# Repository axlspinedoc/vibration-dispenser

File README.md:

<h3 align="center">Dispensador Vibratorio</h3>

<div align="center">

</div>

---

<p align="center"> Automatización de un equipo dispensador de alimentos a granel
    <br> 
</p>

# 🧐 Acerca del proyecto 

Este repositorio contiene el código fuente del sistema operativo de una dispensador a granel utilizando un microcontrolador Amega2560

# 🏁 Preparación necesaria 

1. Instale la herramienta [VSCode](https://code.visualstudio.com)

2. Abra el programa y entre a _File_, _Preferences_, _Extensions_.

3. En el buscador, introduzca _C/C++_ e instale la extensión.

4. Nuevamente en el buscador, introduzca ahora _PlatformIO IDE_ e instale.

5. Una vez instalados correctamente, cada vez que abra VSCode aparecerá la pantalla de inicio con el anuncio "Welcome to PlatformIO"

6. Descargue una copia de este repositorio desde la opción _Code_, _Descargar Zip_. Descomprima en una ubicación conocida.

7. Desde la pestaña de _home_ de PlatformIO, seleccione _import Arduino project_

8. El programa cargara el proyecto y actualizará los documentos dependiendo la computadora donde se abra. *Espere 5 minutos*, esto permitirá que esté listo para programar

9. Para verificar que está listo busque el botón _Build_ en la barra inferior azul, marcado con el símbolo de palomilla

10. Si en el panel inferior aparece la instrucción [SUCCESS], está listo para programar. Conecte el Arduino a su computadora con el cable USB

11. Presione el botón _Upload_ en la barra inferior azul, marcado con una flecha hacia la derecha. Este botón está inmediatamente a la derecha del botón con la palomilla.

12. Pasados 15 segundos, el _Arduino_ se habrá reinicializado. ¡Ha actualizado exitosamente su microcontrolador!

# Para realizar Ajustes

Abra el archivo _utilities.h_ dentro de la carpeta _lib/inc_

Desde aquí puede editarse:

1. Producto a cargar al iniciar el equipo
2. Peso inicial default
3. Tiempo de espera cuando termina de vaciarse la Tolva
4. Selección del modo del relevador
5. Posiciones de la puerta en el estado ABIERTO y CERRADO
6. Sensibilidad de la báscula durante dispensado y vaciado
7. Calibración de báscula
8. Tiempo de señal de _Relay_
9. Tiempo de espera después de dispensar en tolva

Para editar la base de datos de productos abra el archivo _productos.h_ dentro de la carpeta _lib/inc_

Siga las indicaciones del archivo para agregar productos seleccionables desde la pantalla

# ⛏️ Built Using 

- [Visual Studio Code](https://code.visualstudio.com) - IDE
- [PlatformIO](https://platformio.org) - Embedded development IDE
- [Arduino Mega](https://www.arduino.cc) - Prototyping

# ✍️ Authors 

- [@axlspinedoc](https://github.com/axlspinedoc) - Developer

# 🎉 Acknowledgements 

- Amber Macias

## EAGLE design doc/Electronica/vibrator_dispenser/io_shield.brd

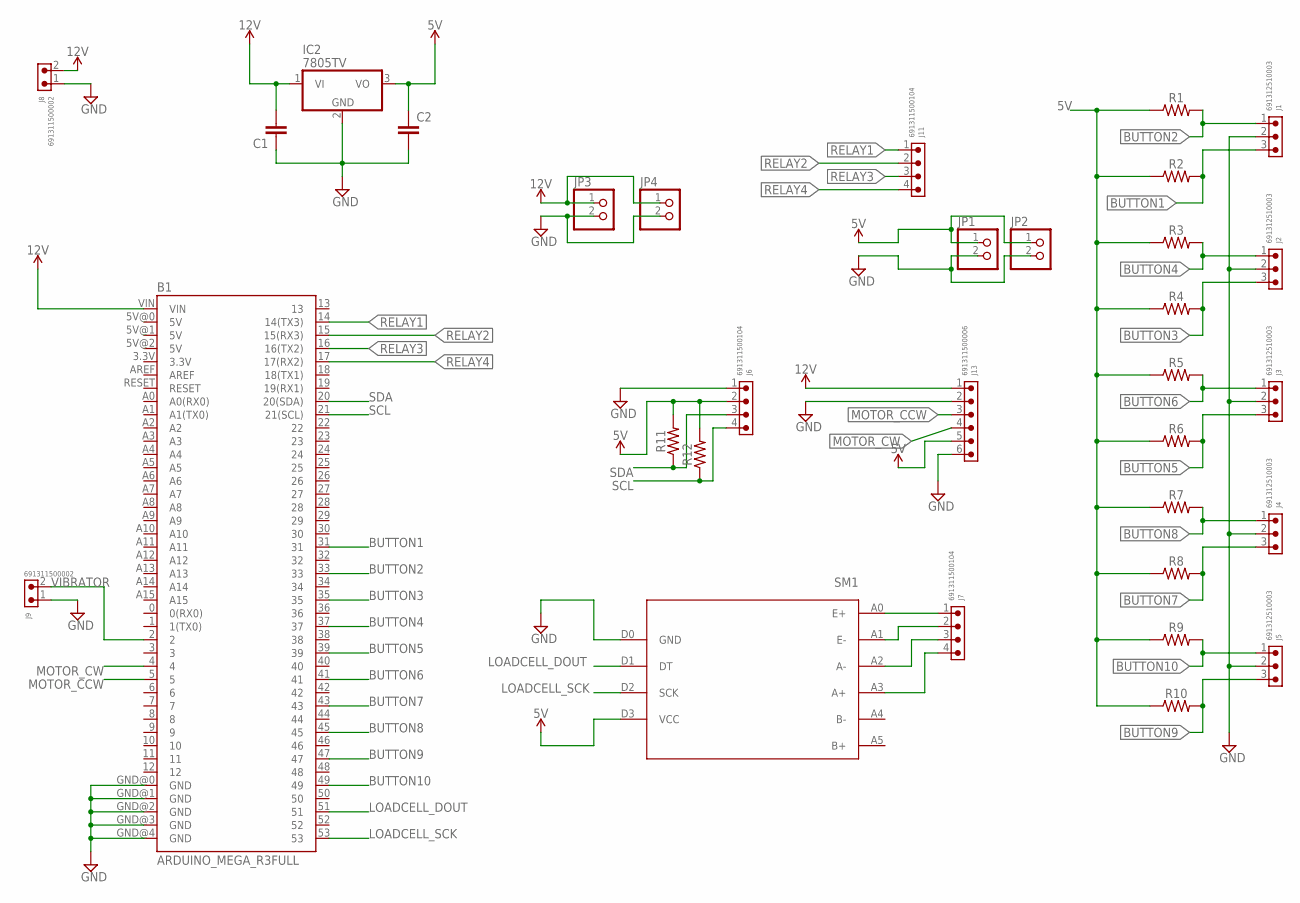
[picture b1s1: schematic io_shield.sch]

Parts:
B1: ARDUINO_MEGA_R3FULL; ARDUINO_MEGA
C1, C2: C-EU050-025X075; C050-025X075
IC2: 7805TV; TO220V
J1, J2, J3, J4, J5: 691312510003
J6, J7, J11: 691311500104
J8, J9: 691311500002
J13: 691311500006
JP1, JP2, JP3, JP4: PINHD-1X2; 1X02
R1, R2, R3, R4, R5, R6, R7, R8, R9, R10, R11, R12: AXIAL-0.3
SM1: HX711

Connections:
5V: C2.1, IC2.3 (VO), J6.2, J13.5, JP1.1, JP2.1, R1.P$1 (1), R2.P$1 (1), R3.P$1 (1), R4.P$1 (1), R5.P$1 (1), R6.P$1 (1), R7.P$1 (1), R8.P$1 (1), R9.P$1 (1), R10.P$1 (1), R11.P$2 (2), R12.P$2 (2), SM1.D3 (VCC)
12V: B1.VIN, C1.2, IC2.1 (VI), J8.2, J13.1, JP3.1, JP4.1
A+: J7.4, SM1.A3 (A+)
A-: J7.3, SM1.A2 (A-)
BUTTON1: B1.31, J1.3, R2.P$2 (2)
BUTTON2: B1.33, J1.1, R1.P$2 (2)
BUTTON3: B1.35, J2.3, R4.P$2 (2)
BUTTON4: B1.37, J2.1, R3.P$2 (2)
BUTTON5: B1.39, J3.3, R6.P$2 (2)
BUTTON6: B1.41, J3.1, R5.P$2 (2)
BUTTON7: B1.43, J4.3, R8.P$2 (2)
BUTTON8: B1.45, J4.1, R7.P$2 (2)
BUTTON9: B1.47, J5.3, R10.P$2 (2)
BUTTON10: B1.49, J5.1, R9.P$2 (2)
E+: J7.1, SM1.A0 (E+)
E-: J7.2, SM1.A1 (E-)
GND: B1.GND@0 (GND), B1.GND@1 (GND), B1.GND@2 (GND), B1.GND@3 (GND), B1.GND@4 (GND), C1.1, C2.2, IC2.2 (GND), J1.2, J2.2, J3.2, J4.2, J5.2, J6.1, J8.1, J9.1, J13.2, J13.6, JP1.2, JP2.2, JP3.2, JP4.2, SM1.D0 (GND)
LOADCELL_DOUT: B1.51, SM1.D1 (DT)
LOADCELL_SCK: B1.53, SM1.D2 (SCK)
MOTOR_CCW: B1.5, J13.3
MOTOR_CW: B1.4, J13.4
RELAY1: B1.14 (14(TX3)), J11.1
RELAY2: B1.15 (15(RX3)), J11.2
RELAY3: B1.16 (16(TX2)), J11.3
RELAY4: B1.17 (17(RX2)), J11.4
SCL: B1.21 (21(SCL)), J6.4, R12.P$1 (1)
SDA: B1.20 (20(SDA)), J6.3, R11.P$1 (1)
VIBRATOR: B1.2, J9.2

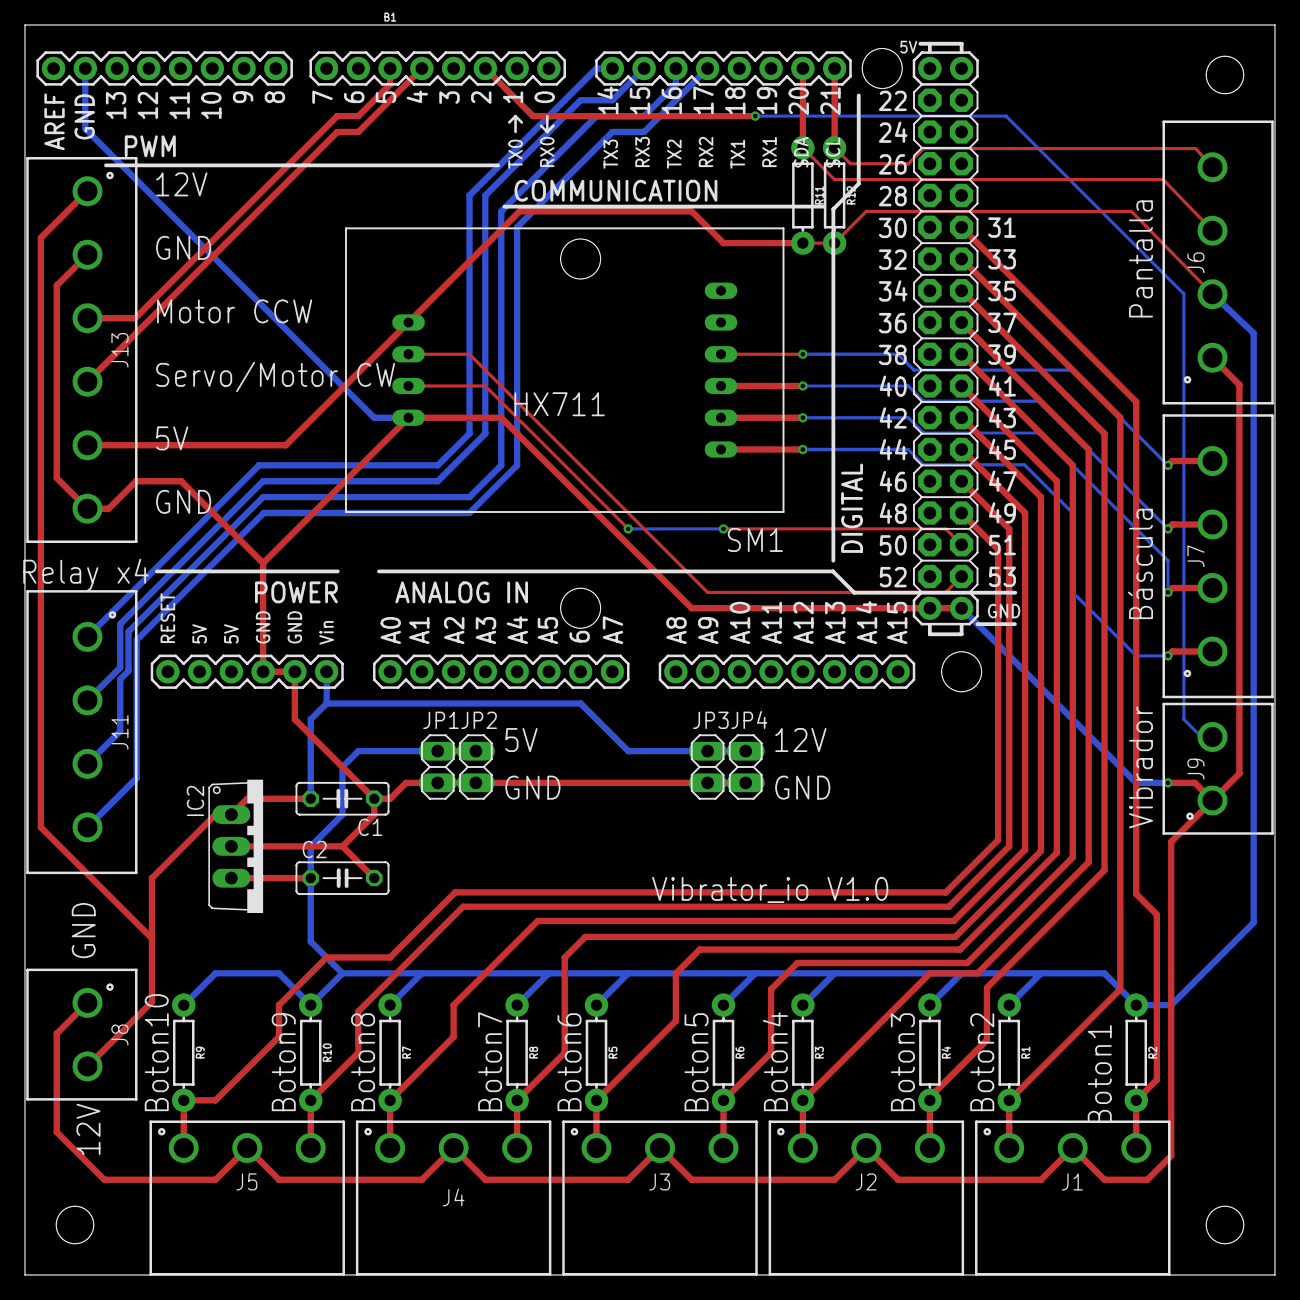
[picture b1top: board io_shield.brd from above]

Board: 2 copper layers, 100.0 x 100.0 mm, 32 parts (0 on the bottom side), 28 nets.

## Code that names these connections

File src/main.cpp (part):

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  analogWrite(DC_CW_PIN,0);
  #endif

  scale.begin(LOADCELL_DOUT_PIN, LOADCELL_SCK_PIN);  
  
  //if (scale.wait_ready_retry(20,100))  
  if (scale.is_ready())
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  setScreen(Screen::STANDBY);  
  
  // Vibrator
  pinMode(VIBRATOR_PIN, OUTPUT);

  // Relays
  pinMode(RELAY1_PIN,OUTPUT); // Vibrador para Tolva
  pinMode(RELAY2_PIN,OUTPUT); // Alarma
  pinMode(RELAY3_PIN,OUTPUT); // Chicharra
  pinMode(RELAY4_PIN,OUTPUT); // --Libre--
  
  // Relay behavior is inverted
  digitalWrite(RELAY1_PIN,HIGH);
  digitalWrite(RELAY2_PIN,HIGH);
  digitalWrite(RELAY3_PIN,HIGH);
  digitalWrite(RELAY4_PIN,HIGH);

}

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        
        // From here, we will delay 2s and jump right into FLUSH
        delay(delay_after_dispense);                
        digitalWrite(RELAY1_PIN,LOW);
                        
        machine_state.setState(control::State::SERVED);        

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      {        
        cancel_button.reset();
        delay(door_delay);
        digitalWrite(RELAY1_PIN,HIGH);                
                                
        timer_alarma=millis();
        
        // Relevador para ALARMA
        digitalWrite(RELAY2_PIN,LOW);        
        while((millis()-timer_alarma)<relay_delay){
          
          if (wrong_weight==true)
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          }
                                        
        }
        digitalWrite(RELAY2_PIN,HIGH);
        digitalWrite(RELAY3_PIN,HIGH);
        buzzer_on=false;
        // erase flag
        wrong_weight=false;
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        if (checkArrowButtons()==Key::SELECT)
        {
          incomingChar='.';
          digitalWrite(RELAY1_PIN,HIGH);
          digitalWrite(RELAY2_PIN,HIGH);
          digitalWrite(RELAY3_PIN,HIGH);
          digitalWrite(RELAY4_PIN,HIGH);
          resetArrowButtons();
          machine_state.setState(control::State::STANDBY);
          setScreen(Screen::STANDBY);
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  {
    if (buzzer_on==true)
    {
      digitalWrite(RELAY3_PIN, HIGH);
      buzzer_on = false;
    }else
    {
      digitalWrite(RELAY3_PIN, LOW);
      buzzer_on = true;
    }
    previous_buzzer_timestamp=millis();    
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
void setVibration(int percentage){
  //int pwm=map(percentage,0,100,0,255);
  //analogWrite(VIBRATOR_PIN,pwm);
  analogWrite(VIBRATOR_PIN,percentage);
}

void errorScreen(String msg){
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
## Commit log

2020-09-14 Created project in PIO
2020-09-16 updated git ignore, added template for clases
2020-09-16 Added some libraries, building simple state machine
2020-09-16 Successful test of State machine. TODO: Test weight change
2020-09-16 Implemented state machine class
2020-09-16 Added library for load cell
2020-09-16 Added liquid crystal library
2020-09-18 Added support for LCD using PIO library
2020-09-18 Added LCD functionality for MH LCDI2C Adapter, replaced previous library. TODO: Implement one time only LCD prints
2020-09-18 MVP with state machine and 20x4 LCD
2020-09-18 Defined keypad library and keys enum
2020-09-18 Added screencom library with functions for each type of menu
2020-09-18 Added support for keypad shield LCD
2020-09-18 Created readme.md with template
2020-09-19 Added keypad library
2020-09-19 Changed board to Arduino Mega
2020-09-19 WIP LCD Debugging, possible bad LCD
2020-09-19 Keypad shield and Arduino Mega fully functional
2020-09-20 WIP button library, broken atm
2020-09-20 Changed button behavior
2020-09-20 Button library fully functional
2020-09-20 Implemented buttons to main. TODO Debug SERVED Stage
2020-09-20 Corrected button logic inside main. Buttons finalized
2020-09-20 Changed tick() function to update() inside button to better reflect behavior
2020-09-20 Keypad functionality testing. WIP Debounce for directional keys
2020-09-20 Testing debounce routine inside Keypad
2020-09-20 WIP Edge detection for keypad in progress
2020-09-21 Scale fully functioning
2020-09-21 Added scale factor to utilities, added HX711 objecto to main. WIP scale implementation
2020-09-21 Scale fully implemented in main
2020-09-23 Tested screencom functionality inside main. Screencom still not developed
2020-09-23 Implemented SETGRAMS screen with blinking cursor. TODO: Implement keys
2020-09-24 Corrected keypad function. Keys are detectable now. TODO: Check debounce
2020-09-24 [debug] Debounce needed. Key detect is functional but only with delays atm
2020-09-25 Debbugged Keypad, fully operational. Removing debounce
2020-09-25 Debounce not needed in keypad. Class finished
2020-09-25 Ready for PR, added scale.is_ready() to avoid hanging while working without scale
2020-09-25 manageWeight() WIP. Keypad readable from function
2020-09-25 WIP manageWeight() redesigned setWeightScreen() to update set_weight continuously
2020-09-25 Basic weight change functionality implemented. Some bugs still to correct
2020-09-25 Preparing for vibrator. WIP function to transform decimal position to power of 10 in ints
2020-09-26 Changed digit addition operation. from pow(10,(14-col)) to a single int[]
2020-09-26 SetWeightScreen function fully functional
2020-09-26 Started implementation of PWM for vibration control. TODO: Add speed control
2020-09-26 Added Scale disconnection detection during dispensing to avoid hanging
2020-09-26 Added progress variable to track filling of funnel. WIP security for scale disconnection
2020-09-26 Added scale strange values detection at DISPENSING state
2020-09-26 Added vibrator variation after set progress point
2020-09-27 updated pins to PCB MVP
2020-09-28 Code of 1st functional prototype
2020-09-30 WIP menu options from STANDBY for TARE, SETGRAMS, and speed control
2020-09-30 Menu changer for standby implemented. TODO: implement speed change
2020-09-30 Recycling setWeight functions for set speed
2020-10-01 Speed changes applied. TODO: Test on board
2020-10-02 Speed change, Tare and Weight change fully implemented and debugged. ready for merge
2020-10-03 Edited Readme.md
2020-10-05 Updated file structure
2020-10-09 Added necessary changes for Q3, TODO: Product selector
2020-10-10 Updated code according to emergency code changes
2020-10-10 Inverted Servo
2020-10-10 Changed alarm behavior. Now activates after flusj
2020-10-12 Added sensibility and scale values to be configured by user from utilities.h
2020-10-12 Adjusted Scale slope
2020-10-13 Created productos.h, preparing for menu implementation
2020-10-13 WIP Product selection from menu. TODO: Get String name of product and prompt in menu
2020-10-13 WIP Created test for showing product id only. Testing speed that product parameters are read
2020-10-13 Added Title to product change menu
2020-10-13 [Bugfix] Product code was not shown on Menu tests. Changed displayed value
2020-10-13 [Bugfix] Added missing resetKeys to manageProducts switch
2020-10-13 Product name prompt implemented, awaiting tests
2020-10-13 [bugfix] Print currently loaded product at the start
2020-10-13 Changed door_button logic to cancel button. At any time it can be pressed and will transfer to SERVED state
2020-10-13 Added pause configs for relay, served
2020-10-13 Fixed Relay delay time
2020-11-10 Added delay for keypad.reset to avoid bouncing. Increased SENSIBILIDAD_DISPENSADO from 3 to 5
2020-11-13 Quick patch to adjust Keypad sensibility
2020-12-03 Change LCD to I2C library and bus. Tests succesful
2020-12-03 Changed Keypad for io::Button objects. Compilation succesful
2020-12-04 Changed all pinouts to accomodate new vibrator_io V1.0 board
2020-12-04 Integrated relays 1 and 2
2020-12-04 Debugged Relay module, relay ouputs are reversed
2020-12-04 Implemented new sampling method for reading scale
2020-12-04 Device now knows when wrong weight was dispensed
2020-12-04 Buzzer integrated
2020-12-05 Final code, Schematics and BOM integrated

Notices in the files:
parts and their libraries:
SparkFun-Boards: Licensing: Creative Commons ShareAlike 4.0 International - https://creativecommons.org/licenses/by-sa/4.0
Eagle_WR-TBL Pluggable Connector: Copyright: Würth Elektronik
